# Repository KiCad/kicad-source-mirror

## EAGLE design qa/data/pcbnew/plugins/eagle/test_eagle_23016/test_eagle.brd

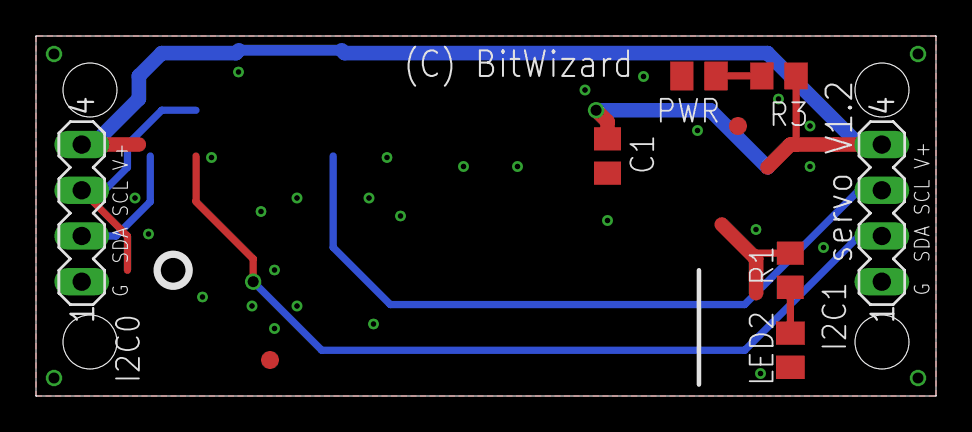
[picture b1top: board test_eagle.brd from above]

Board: 2 copper layers, 50.0 x 20.0 mm, 13 parts (0 on the bottom side), 6 nets.

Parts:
AFIT1, AFIT2: FIDUCIAL1; FID1
C1: 100n; C0805
I2C0, I2C1: MA04-1
LED2: G; M0805
PWR: G; M0805
R1, R3: 47k; R0805
U$2, U$3, U$4, U$5: MOUNTING_HOLE

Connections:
GND: C1.2, I2C0.1, I2C1.1, LED2.2, PWR.2
unnamed: I2C0.2, I2C1.2
unnamed: PWR.1, R3.1
unnamed: I2C0.3, I2C1.3
unnamed: LED2.1, R1.1
VCC: C1.1, I2C0.4, I2C1.4, R3.2
